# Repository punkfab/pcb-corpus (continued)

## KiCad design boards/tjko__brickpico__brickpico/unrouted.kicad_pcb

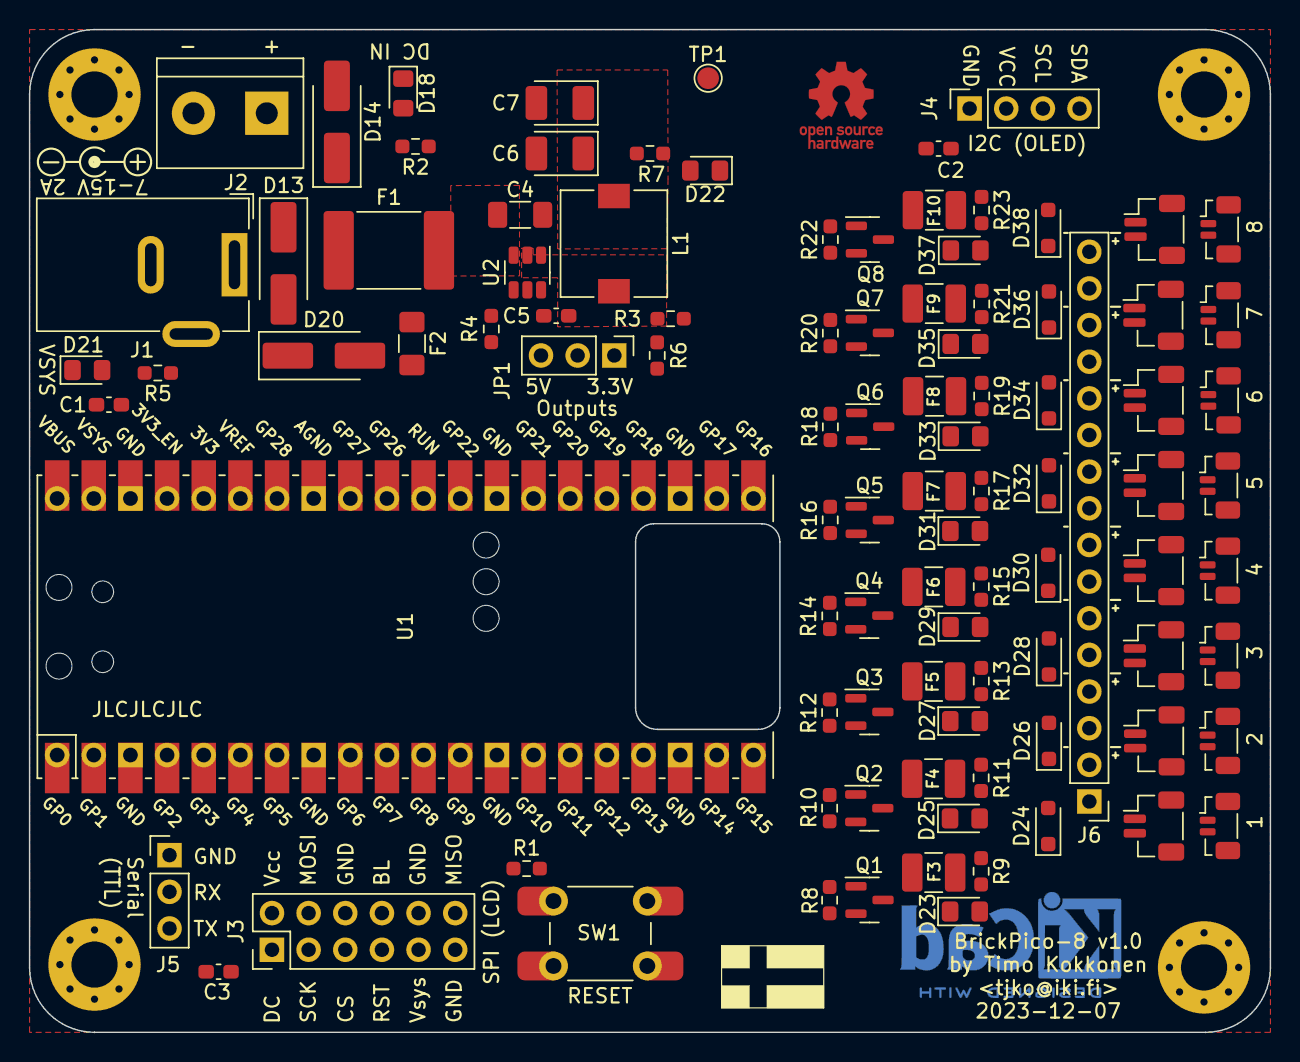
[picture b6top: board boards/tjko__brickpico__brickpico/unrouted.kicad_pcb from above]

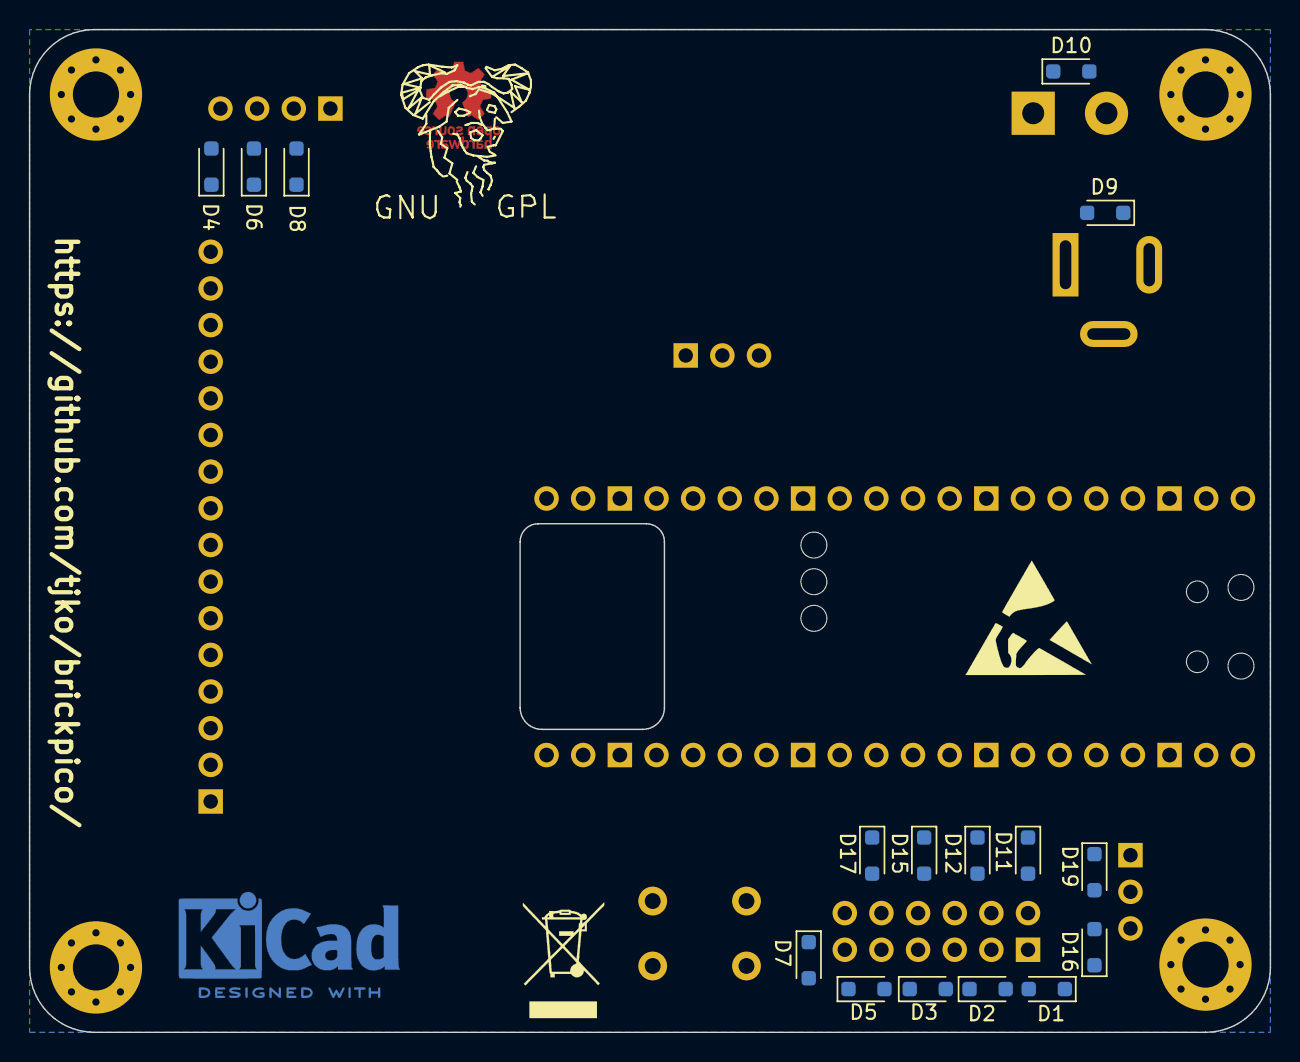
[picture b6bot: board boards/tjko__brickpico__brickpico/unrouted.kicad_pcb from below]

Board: 4 copper layers, 86.0 x 69.5 mm, 118 parts (16 on the bottom side), 68 nets, no tracks yet.

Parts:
C1, C2, C3, C5: 0.1uF; C_0603_1608Metric_Pad1.08x0.95mm_HandSolder
C4: 10uF 50V; C_1206_3216Metric_Pad1.33x1.80mm_HandSolder
C6, C7: 22uF 16V; CP_EIA-3528-21_Kemet-B_Pad1.50x2.35mm_HandSolder
D1, D2, D3, D4, D5, D6, D8, D11, D12, D15, D16, D17, D19: 3.3V; D_SOD-323_HandSoldering
D7, D24, D26, D28, D30, D32, D34, D36, D38: 5V; D_SOD-323_HandSoldering
D9, D10: 12V; D_SOD-323_HandSoldering
D13, D14: SK54A-LTP; D_SMA_Handsoldering
D18, D21, D22, D23, D25, D27, D29, D31, D33, D35, D37: LED; LED_0805_2012Metric_Pad1.15x1.40mm_HandSolder
D20: SM5819PL 1A; D_SMA_Handsoldering
F1: Polyfuse 3A; Fuse_2920_7451Metric_Pad2.10x5.45mm_HandSolder
F2: Polyfuse 500mA; Fuse_1206_3216Metric_Pad1.42x1.75mm_HandSolder
F3, F4, F5, F6, F7, F8, F9, F10: Polyfuse 200mA; Fuse_1210_3225Metric_Pad1.42x2.65mm_HandSolder
H1, H2, H3, H4: MountingHole_Pad; MountingHole_3.2mm_M3_Pad_Via
J1: DC Connector; BarrelJack_Wuerth_6941xx301002
J2: Terminal Block; TerminalBlock_bornier-2_P5.08mm
J3: SPI (LCD); PinHeader_2x06_P2.54mm_Vertical
J4: I2C (OLED); PinSocket_1x04_P2.54mm_Vertical
J5: Serial (TTL); PinHeader_1x03_P2.54mm_Vertical
J6: Conn_01x16; PinHeader_1x16_P2.54mm_Vertical
J7, J8, J9, J10, J11, J12, J13, J14: JST SUR; JST_SUR_BM02B-SURS-TF_1x02-1MP_P0.80mm_Vertical
J15, J16, J17, J18, J19, J20, J21, J22: JST SRS; JST_SH_BM02B-SRSS-TB_1x02-1MP_P1.00mm_Vertical
JP1: Conn_01x03; PinHeader_1x03_P2.54mm_Vertical
L1: 3.3uH; L_7.3x7.3_H3.5_HandSolder
Q1, Q2, Q3, Q4, Q5, Q6, Q7, Q8: 2N7002K; SOT-23
R1, R8, R10, R12, R14, R16, R18, R20, R22: 1K; R_0603_1608Metric_Pad0.98x0.95mm_HandSolder
R2: 49.9K; R_0603_1608Metric_Pad0.98x0.95mm_HandSolder
R3: 56.2K; R_0603_1608Metric_Pad0.98x0.95mm_HandSolder
R4, R5, R7, R9, R11, R13, R15, R17, R19, R21, R23: 10K; R_0603_1608Metric_Pad0.98x0.95mm_HandSolder
R6: 82K; R_0603_1608Metric_Pad0.98x0.95mm_HandSolder
SW1: Reset; SW_PUSH_6mm_SMD_2
TP1: TestPoint; TestPoint_Pad_D1.5mm
U1: Pico; RPi_Pico_PicoW_SMD_TH
U2: AP62300TWU; TSOT-26

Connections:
3V3: C2.2, C3.1, D8.2 (A2), D11.2 (A2), D15.2 (A2), J3.2, J3.8, J4.2, U1.36 (3V3)
/LED Connectors/Output 1/OUT_N: D23.1 (K), D24.1 (A1), J6.1, J7.2, J15.2, Q1.3 (D)
/LED Connectors/Output 1/OUT_P: D24.2 (A2), F3.2, J6.2, J7.1, J15.1, R9.1
/LED Connectors/Output 2/OUT_N: D25.1 (K), D26.1 (A1), J6.3, J8.2, J16.2, Q2.3 (D)
/LED Connectors/Output 2/OUT_P: D26.2 (A2), F4.2, J6.4, J8.1, J16.1, R11.1
/LED Connectors/Output 3/OUT_N: D27.1 (K), D28.1 (A1), J6.5, J9.2, J17.2, Q3.3 (D)
/LED Connectors/Output 3/OUT_P: D28.2 (A2), F5.2, J6.6, J9.1, J17.1, R13.1
/LED Connectors/Output 4/OUT_N: D29.1 (K), D30.1 (A1), J6.7, J10.2, J18.2, Q4.3 (D)
/LED Connectors/Output 4/OUT_P: D30.2 (A2), F6.2, J6.8, J10.1, J18.1, R15.1
/LED Connectors/Output 5/OUT_N: D31.1 (K), D32.1 (A1), J6.9, J11.2, J19.2, Q5.3 (D)
/LED Connectors/Output 5/OUT_P: D32.2 (A2), F7.2, J6.10, J11.1, J19.1, R17.1
/LED Connectors/Output 6/OUT_N: D33.1 (K), D34.1 (A1), J6.11, J12.2, J20.2, Q6.3 (D)
/LED Connectors/Output 6/OUT_P: D34.2 (A2), F8.2, J6.12, J12.1, J20.1, R19.1
/LED Connectors/Output 7/OUT_N: D35.1 (K), D36.1 (A1), J6.13, J13.2, J21.2, Q7.3 (D)
/LED Connectors/Output 7/OUT_P: D36.2 (A2), F9.2, J6.14, J13.1, J21.1, R21.1
/LED Connectors/Output 8/OUT_N: D37.1 (K), D38.1 (A1), J6.15, J14.2, J22.2, Q8.3 (D)
/LED Connectors/Output 8/OUT_P: D38.2 (A2), F10.2, J6.16, J14.1, J22.1, R23.1
CS: D3.2 (A2), J3.5, U1.7 (GPIO5)
DC: D1.2 (A2), J3.1, U1.29 (GPIO22)
DC_IN: C4.2, F1.2, R2.1, U2.3 (IN)
GND: C1.2, C2.1, C3.2, C4.1, C6.2, C7.2, D1.1 (A1), D2.1 (A1), D3.1 (A1), D4.1 (A1), D5.1 (A1), D6.1 (A1), D7.1 (A1), D8.1 (A1), D9.1 (A1), D10.2 (A2), D11.1 (A1), D12.1 (A1), D15.1 (A1), D16.1 (A1), D17.1 (A1), D18.1 (K), D19.1 (A1), D21.1 (K), D22.1 (K), H1.1, H2.1, H3.1, H4.1, J1.2, J2.2, J3.6, J3.10, J3.11, J4.1, J5.1, Q1.2 (S), Q2.2 (S), Q3.2 (S), Q4.2 (S), Q5.2 (S), Q6.2 (S), Q7.2 (S), Q8.2 (S), R4.1, SW1.2, U1.3 (GND), U1.8 (GND), U1.13 (GND), U1.18 (GND), U1.23 (GND), U1.28 (GND), U1.38 (GND), U2.1 (GND)
LED_PWR_1: C6.1, C7.1, F2.1, F3.1, F4.1, F5.1, F6.1, F7.1, F8.1, F9.1, F10.1, L1.2, R3.2, R6.2, R7.1, TP1.1
MISO: D17.2 (A2), J3.12, U1.6 (GPIO4)
MOSI: D12.2 (A2), J3.4, U1.5 (GPIO3)
unnamed: D10.1 (A1), D14.2 (A), J2.1
unnamed: D9.2 (A2), D13.2 (A), J1.1
unnamed: D13.1 (K), D14.1 (K), F1.1
unnamed: D18.2 (A), R2.2
unnamed: D20.2 (A), F2.2
unnamed: D21.2 (A), R5.2
unnamed: D22.2 (A), R7.2
unnamed: D23.2 (A), R9.2
unnamed: D25.2 (A), R11.2
unnamed: D27.2 (A), R13.2
unnamed: D29.2 (A), R15.2
unnamed: D31.2 (A), R17.2
unnamed: D33.2 (A), R19.2
unnamed: D35.2 (A), R21.2
unnamed: D37.2 (A), R23.2
unnamed: JP1.1 (A), R6.1
unnamed: JP1.2 (C), R3.1, R4.2, U2.4 (FB)
unnamed: Q1.1 (G), R8.1
unnamed: Q2.1 (G), R10.1
unnamed: Q3.1 (G), R12.1
unnamed: Q4.1 (G), R14.1
unnamed: Q5.1 (G), R16.1
unnamed: Q6.1 (G), R18.1
unnamed: Q7.1 (G), R20.1
unnamed: Q8.1 (G), R22.1
unnamed: R1.2, SW1.1
unnamed: R1.1, U1.30 (RUN)
unnamed: C5.1, U2.6 (BST)
unnamed: C5.2, L1.1, U2.2 (SW)
PWM0A: R8.2, U1.21 (GPIO16)
PWM0B: R10.2, U1.22 (GPIO17)
PWM1A: R12.2, U1.24 (GPIO18)
PWM1B: R14.2, U1.25 (GPIO19)
PWM2A: R16.2, U1.26 (GPIO20)
PWM2B: R18.2, U1.27 (GPIO21)
PWM3A: R20.2, U1.9 (GPIO6)
PWM3B: R22.2, U1.10 (GPIO7)
RST: D5.2 (A2), J3.7, U1.34 (GPIO28_ADC2)
RX: D19.2 (A2), J5.2, U1.2 (GPIO1)
SCK: D2.2 (A2), J3.3, U1.4 (GPIO2)
SCL: D6.2 (A2), J4.3, U1.32 (GPIO27_ADC1)
SDA: D4.2 (A2), J4.4, U1.31 (GPIO26_ADC0)
TX: D16.2 (A2), J5.3, U1.1 (GPIO0)
VSYS: C1.1, D7.2 (A2), D20.1 (K), J3.9, R5.1, U1.39 (VSYS)

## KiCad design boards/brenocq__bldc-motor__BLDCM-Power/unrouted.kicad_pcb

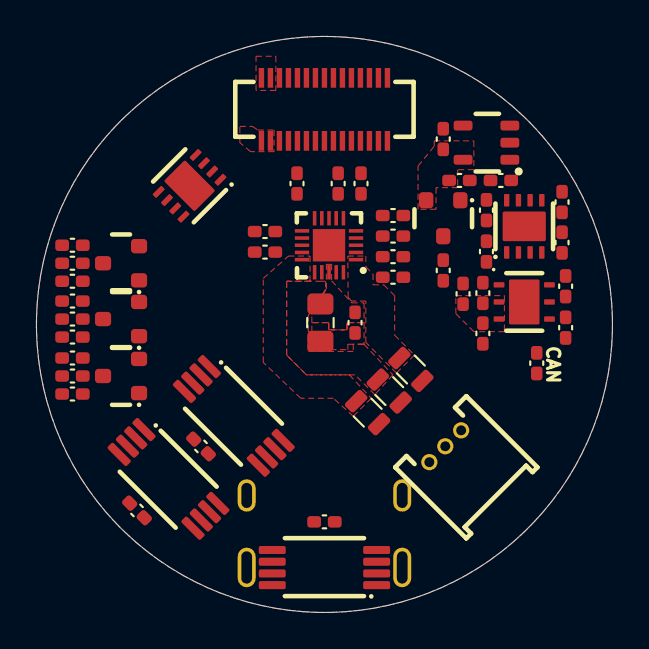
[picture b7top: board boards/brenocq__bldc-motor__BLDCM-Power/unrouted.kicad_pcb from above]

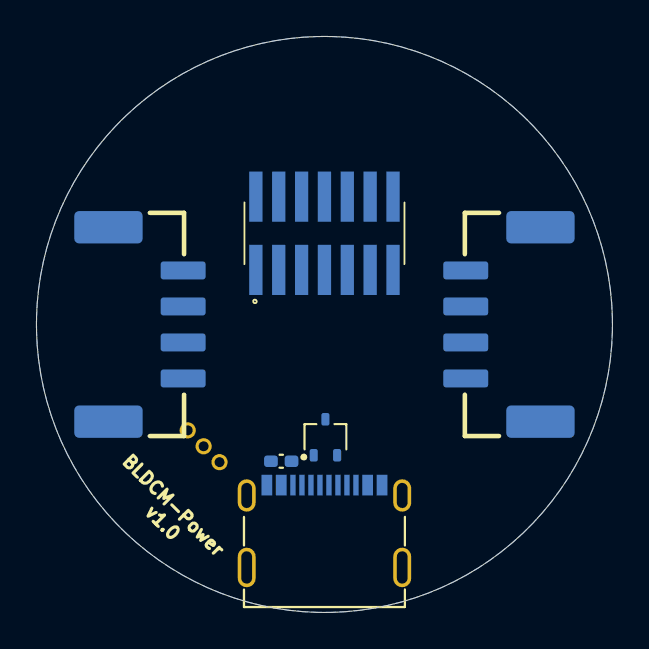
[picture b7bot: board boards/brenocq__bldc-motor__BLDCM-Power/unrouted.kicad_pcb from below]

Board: 4 copper layers, 32.0 x 32.0 mm, 60 parts (6 on the bottom side), 43 nets, no tracks yet.

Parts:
C1, C2, C5, C6, C7, C8, C10, C13, C14: 100nF; C_0402
C3, C4, C11, C12: 1uF; C_0402
C9: 10uF; C_0805
C15, C16, C17: 10nF; C_0402
D3: ESDA25W; SOT-323
J1: 501920-3001
J2: 53048-0310
J3, J4: 505578-0460
J5: FTSH-107-01-L-DV-K; FTSH-107-01-L-DV-K-TR
J6: 217179-0001
R1, R19, R21, R23: 20K; R_0402
R2, R4, R12: KRL1220 50m; KRL1220
R3: 5.1K; R_0402
R5, R6, R7, R8, R9, R10, R14, R16, R17, R18: 100K; R_0402
R11: 120; R_0402
R13, R20, R22, R24: 10K; R_0402
R15: 500; R_0402
U1, U4, U6: INA240A1PWR; TSSOP-8
U2: LDLN030G33R; TSOT-23-5
U3: TMC6300-LA; QFN-20
U5: TCAN1462; VSON-8
U7, U10, U11, U12: BAT54S; SOT-23
U8: LDO40LPU50RY; DFN-6-3x3
U9: TPS2115ADRB; VSON-8

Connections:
3.3V: C1.1, C4.2, C5.1, C6.2, C8.1, J1.1, J1.3, J5.3 (VCC), R14.1, U1.5 (VCC), U1.6 (REF2), U2.5 (OUT), U3.11 (VIO/~STDBY), U4.5 (VCC), U4.6 (REF2), U5.3 (VCC), U5.5 (VIO), U6.5 (VCC), U6.6 (REF2), U7.2, U10.2, U11.2, U12.2
5V: C3.2, J1.2, J1.4, U2.1 (IN), U2.3 (EN), U9.7 (OUT)
/CAN.DN: J3.2, J4.2, R11.1, U5.6 (CANL)
/CAN.DP: J3.1, J4.1, R11.2, U5.7 (CANH)
/CAN.RX: J1.7, U5.4 (RXD)
/CAN.TX: J1.5, U5.1 (TXD)
/CURR.U: J1.10, U1.8 (OUT)
/CURR.V: J1.12, U4.8 (OUT)
/CURR.W: J1.14, U6.8 (OUT)
/Power Management/VIN_5V: C12.2, C13.1, R18.1, U8.4 (VOUT), U8.5 (SENSE), U9.6 (IN2)
/RST: J1.17, J5.12 (NRST)
/SWCLK: J1.21, J5.6 (SWCLK)
/SWDIO: J1.23, J5.4 (SWDIO)
/SWO: J1.19, J5.8 (SWO)
/TMC.DIAG: J1.18, U3.12 (DIAG)
/TMC.U.IN: R2.1, U1.3 (IN-), U3.15 (U)
/TMC.U.OUT: J2.1, R2.2, R19.2, U1.2 (IN+)
/TMC.UH: J1.20, R5.2, U3.3 (UH)
/TMC.UL: J1.22, R6.2, U3.6 (UL)
/TMC.V.IN: R4.1, U3.17 (V), U4.3 (IN-)
/TMC.V.OUT: J2.2, R4.2, R21.2, U4.2 (IN+)
/TMC.VH: J1.24, R7.2, U3.4 (VH)
/TMC.VL: J1.26, R8.2, U3.10 (VL)
/TMC.W.IN: R12.1, U3.1 (W), U6.3 (IN-)
/TMC.W.OUT: J2.3, R12.2, R23.2, U6.2 (IN+)
/TMC.WH: J1.28, R9.2, U3.5 (WH)
/TMC.WL: J1.30, R10.2, U3.7 (WL)
/USB.DN: D3.1, J1.27, J6.A7 (D-), J6.B7 (D-2)
/USB.DP: D3.2, J1.25, J6.A6 (D+), J6.B6 (D+2)
/VCP.RX: J1.13, J5.13 (VCP_RX)
/VCP.TX: J1.15, J5.14 (VCP_TX)
/VOLT.SRC: J1.29, R1.1, R13.2, U7.3
/VOLT.U: C17.2, J1.16, R19.1, R20.2, U10.3
/VOLT.V: C15.2, J1.9, R21.1, R22.2, U11.3
/VOLT.W: C16.2, J1.11, R23.1, R24.2, U12.3
GND: C1.2, C3.1, C4.1, C5.2, C6.1, C7.1, C8.2, C9.1, C10.1, C11.1, C12.1, C13.2, C14.2, C15.1, C16.1, C17.1, D3.3, J1.6, J1.8, J3.4, J4.4, J5.5 (GND), J5.7 (GND), J5.11 (GND_D), J6.A1_B12 (GND), J6.B1_A12 (GND), J6.SH1 (SHIELD), J6.SH2 (SHIELD), J6.SH3 (SHIELD), J6.SH4 (SHIELD), R3.1, R5.1, R6.1, R7.1, R8.1, R9.1, R10.1, R13.1, R15.2, R16.2, R17.2, R18.2, R20.1, R22.1, R24.1, U1.4 (GND), U1.7 (REF1), U2.2 (GND), U3.8 (GND), U3.9 (GND), U3.14 (GND), U3.16 (BRUV), U3.20 (BRW), U3.21 (PAD), U4.4 (GND), U4.7 (REF1), U5.2 (GND), U5.8 (STB), U5.PAD, U6.4 (GND), U6.7 (REF1), U7.1, U8.1 (GND), U8.PAD, U9.3 (D1), U9.5 (GND), U9.PAD, U10.1, U11.1, U12.1
unnamed: J6.A5 (CC1), R3.2
unnamed: R14.2, U2.4 (PG)
unnamed: C7.2, U3.13 (1.8VOUT)
unnamed: C2.1, U3.2 (VCP)
unnamed: R15.1, U9.4 (ILIM)
VBUS: C14.1, J6.A4_B9 (VBUS), J6.B4_A9 (VBUS), R17.1, U9.2 (D0), U9.8 (IN1)
VIN: C2.2, C9.2, C10.2, C11.2, J3.3, J4.3, R1.2, R16.1, U3.18 (VS), U8.2 (EN), U8.3 (VIN)

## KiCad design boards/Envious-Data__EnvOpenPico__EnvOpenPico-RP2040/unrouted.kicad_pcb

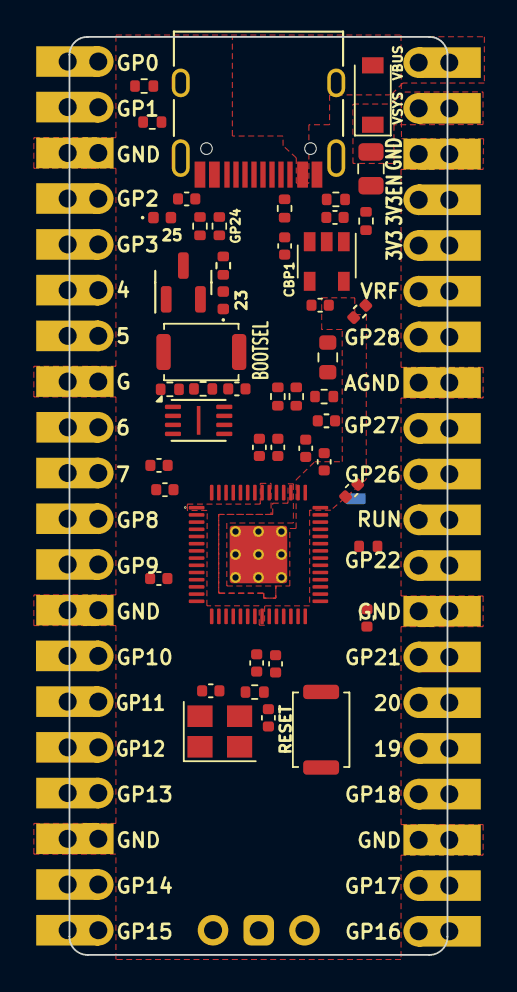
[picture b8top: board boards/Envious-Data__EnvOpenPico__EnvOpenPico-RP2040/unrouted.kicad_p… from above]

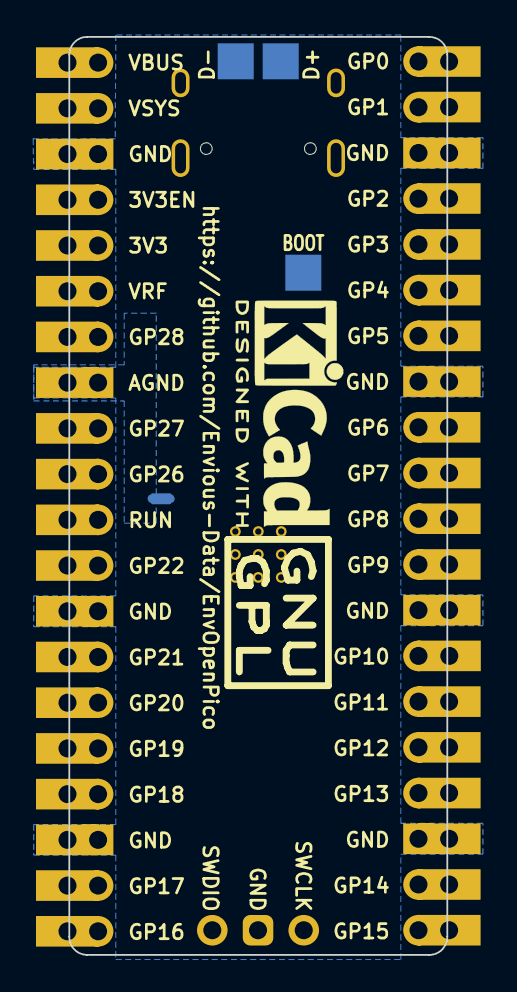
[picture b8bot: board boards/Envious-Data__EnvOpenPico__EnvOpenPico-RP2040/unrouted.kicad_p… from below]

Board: 2 copper layers, 21.0 x 51.0 mm, 55 parts (6 on the bottom side), 64 nets, no tracks yet.

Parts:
C1, C4, C17: 10uf 0402; C_0402_1005Metric
C2, C19: 22pf 0402; C_0402_1005Metric
C3: 1uf 0402; C_0402_1005Metric
C5, C6, C7, C8, C11, C13, C14, C15, C16, C18: 100nf 0402; C_0402_1005Metric
C10, C102: 2.2uF 0402; C_0402_1005Metric
C101: 0.1uf 0402; C_0402_1005Metric
CBP1: 10uf 0402; C_0402_1005Metric
D1: 1N5817W; D_SOD-123
F1: 0805L050WR; Fuse_0805_2012Metric
FB1: FerriteBead 0402; R_0402_1005Metric
FLASH1: W25Q16JVUXIQ; Winbond_USON-8-1EP_3x2mm_P0.5mm_EP0.2x1.6mm
GP23_LED1: GP23 LED_0402; LED_0402_1005Metric
GPIO24_RESISTOR1: 1K 0402; R_0402_1005Metric
GPIO25_LED1: LED_0402; LED_0402_1005Metric
GPIO25_RESISTOR1: 470 0402; R_0402_1005Metric
J1: USB_C_Receptacle_USB2.0; USB_C_Receptacle_HRO_TYPE-C-31-M-12
J2: Button; SW_Push_SPST_NO_Alps_SKRK
J3, J4: 2.54mm header 01x20; PinHeader_1x20_P2.54mm_Vertical
J5: Conn_01x03_Male; PinHeader_1x03_P2.54mm_Vertical
NT1: NetTie_2; NetTie-2_SMD_Pad0.5mm
Q1: SI2301B; SOT-23
R1, R11: 1K 0402; R_0402_1005Metric
R2, R103: 10K 0402; R_0402_1005Metric
R3, R4: 27r 0402 resistor; R_0402_1005Metric
R5, R6: 5.1K 0402; R_0402_1005Metric
R7: 100K 0402; R_0402_1005Metric
R9: 200 0603; R_0603_1608Metric
R10: 1 0402; R_0402_1005Metric
R101: 5.6K 0402; R_0402_1005Metric
R102: 220 0402; R_0402_1005Metric
RSW1: TSA343G00-250J2; SW_Push_SPST_NO_Alps_SKRK
TP1, TP2, TP3: TestPoint; CustomTestPoint
U1: SOT-23-5 5.5V 3.3V 500mA; SOT-23-5
U3: RP2040; RP2040-QFN-56
Y1: 3225_4P 12MHz; Crystal_SMD_3225-4Pin_3.2x2.5mm

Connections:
3V3_EN: J4.4, R7.1, U1.3 (EN)
+1V1: C3.1, C6.1, C7.1, U3.23 (DVDD), U3.45 (VREG_VOUT), U3.50 (DVDD)
+3V3: C4.1, C5.1, C8.1, C10.1, C11.1, C13.1, C14.1, C15.1, C16.1, C17.1, C18.1, FLASH1.8 (VCC), J4.5, Q1.2 (S), R2.1, R9.1, U1.5 (OUT), U3.1 (IOVDD), U3.10 (IOVDD), U3.22 (IOVDD), U3.33 (IOVDD), U3.42 (IOVDD), U3.44 (VREG_IN), U3.48 (USB_VDD), U3.49 (IOVDD)
/ADC_VREF: J4.6, R9.2, R10.1
/GPIO0: J3.20, U3.2 (GPIO0)
/GPIO1: J3.19, U3.3 (GPIO1)
/GPIO2: J3.17, U3.4 (GPIO2)
/GPIO3: J3.16, U3.5 (GPIO3)
/GPIO4: J3.15, U3.6 (GPIO4)
/GPIO5: J3.14, U3.7 (GPIO5)
/GPIO6: J3.12, U3.8 (GPIO6)
/GPIO7: J3.11, U3.9 (GPIO7)
/GPIO8: J3.10, U3.11 (GPIO8)
/GPIO9: J3.9, U3.12 (GPIO9)
/GPIO10: J3.7, U3.13 (GPIO10)
/GPIO11: J3.6, U3.14 (GPIO11)
/GPIO12: J3.5, U3.15 (GPIO12)
/GPIO13: J3.4, U3.16 (GPIO13)
/GPIO14: J3.2, U3.17 (GPIO14)
/GPIO15: J3.1, U3.18 (GPIO15)
/GPIO16: J4.20, U3.27 (GPIO16)
/GPIO17: J4.19, U3.28 (GPIO17)
/GPIO18: J4.17, U3.29 (GPIO18)
/GPIO19: J4.16, U3.30 (GPIO19)
/GPIO20: J4.15, U3.31 (GPIO20)
/GPIO21: J4.14, U3.32 (GPIO21)
/GPIO22: J4.12, U3.34 (GPIO22)
/GPIO23: Q1.1 (G), U3.35 (GPIO23)
/GPIO24: R101.2, R103.1, U3.36 (GPIO24)
/GPIO25: GPIO25_RESISTOR1.2, U3.37 (GPIO25)
/GPIO26_ADC0: J4.10, U3.38 (GPIO26_ADC0)
/GPIO27_ADC1: J4.9, U3.39 (GPIO27_ADC1)
/GPIO28_ADC2: J4.7, U3.40 (GPIO28_ADC2)
/QSPI_SCLK: FLASH1.6 (CLK), U3.52 (QSPI_SCLK)
/QSPI_SD0: FLASH1.5 (DI(IO0)), U3.53 (QSPI_SD0)
/QSPI_SD1: FLASH1.2 (DO(IO1)), U3.55 (QSPI_SD1)
/QSPI_SD2: FLASH1.3 (IO2), U3.54 (QSPI_SD2)
/QSPI_SD3: FLASH1.7 (IO3), U3.51 (QSPI_SD3)
/QSPI_SS: FLASH1.1 (~CS), R1.1, R2.2, U3.56 (QSPI_SS)
/RUN: J4.11, RSW1.2, U3.26 (RUN)
/SWCLK: J5.1, U3.24 (SWCLK)
/SWD: J5.3, U3.25 (SWD)
/~USB_BOOT: J2.1, R1.2, TP3.1
AGND: J4.8, NT1.2
GND: C1.2, C2.1, C3.2, C4.2, C5.2, C6.2, C7.2, C8.2, C10.2, C11.2, C13.2, C14.2, C15.2, C16.2, C17.2, C18.2, C19.1, C101.1, C102.2, CBP1.2, FLASH1.4 (GND), FLASH1.9 (EP), GP23_LED1.1 (K), GPIO25_LED1.1 (K), J1.A1 (GND), J1.A12 (GND), J1.B1 (GND), J1.B12 (GND), J2.2, J3.3, J3.8, J3.13, J3.18, J4.3, J4.13, J4.18, J5.2, NT1.1, R5.1, R6.1, R102.2, R103.2, RSW1.1, U1.2 (GND), U3.19 (TESTEN), U3.57 (GND), Y1.2, Y1.4
unnamed: C19.2, R11.2, Y1.3
unnamed: F1.1, FB1.1
unnamed: GP23_LED1.2 (A), GPIO24_RESISTOR1.1
unnamed: GPIO25_LED1.2 (A), GPIO25_RESISTOR1.1
unnamed: J1.A5 (CC1), R5.2
unnamed: J1.B5 (CC2), R6.2
unnamed: C101.2, J1.S1 (SHIELD), R102.1
unnamed: GPIO24_RESISTOR1.2, Q1.3 (D)
unnamed: CBP1.1, U1.4 (BP)
unnamed: C1.1, FB1.2, U1.1 (IN)
unnamed: C102.1, R10.2, U3.43 (ADC_AVDD)
unnamed: R4.2, U3.46 (USB_DM)
unnamed: R3.2, U3.47 (USB_DP)
USB_D+: J1.A6 (D+), J1.B6 (D+), R3.1, TP1.1
USB_D-: J1.A7 (D-), J1.B7 (D-), R4.1, TP2.1
VBUS: D1.2 (A), J1.A4 (VBUS), J1.A9 (VBUS), J1.B4 (VBUS), J1.B9 (VBUS), J4.1, R101.1
VSYS: D1.1 (K), F1.2, J4.2, R7.2
XIN: C2.2, U3.20 (XIN), Y1.1
XOUT: R11.1, U3.21 (XOUT)
